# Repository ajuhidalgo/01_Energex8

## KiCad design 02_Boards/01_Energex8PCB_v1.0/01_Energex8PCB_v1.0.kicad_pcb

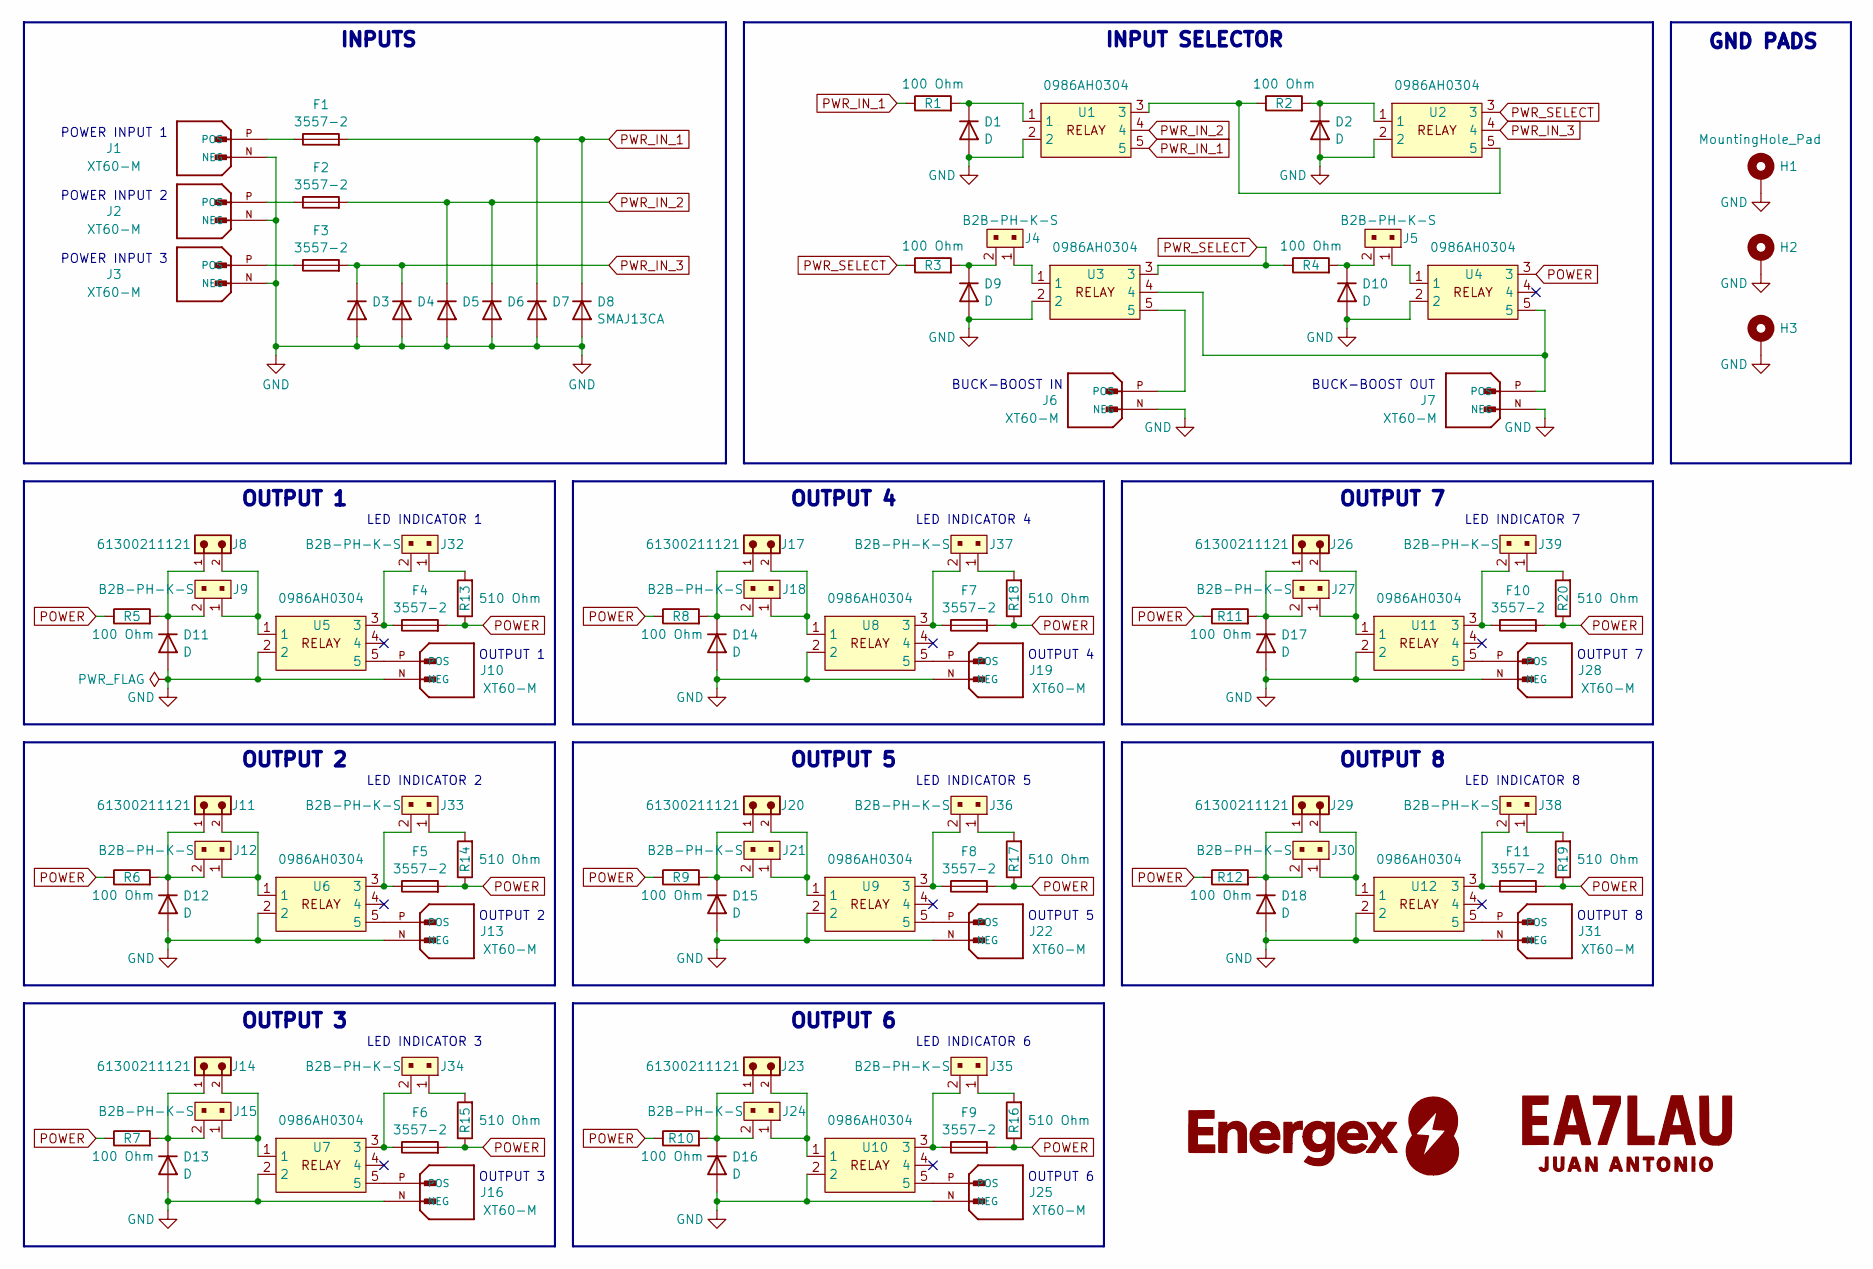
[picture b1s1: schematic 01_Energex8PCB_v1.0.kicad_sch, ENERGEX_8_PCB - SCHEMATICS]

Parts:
D1, D2, D9, D10, D11, D12, D13, D14, D15, D16, D17, D18: D; D_1206_3216Metric
D3, D4, D5, D6, D7, D8: SMAJ13CA; D_SMA
F1, F2, F3, F4, F5, F6, F7, F8, F9, F10, F11: 3557-2; keystone_electronics_3557-2
H1, H2, H3: MountingHole_Pad; MountingHole_3.2mm_M3_Pad_Via
J1, J2, J3, J6, J7, J10, J13, J16, J19, J22, J25, J28, J31: XT60-M; PARTREV V1.2
J4, J5, J9, J12, J15, J18, J21, J24, J27, J30, J32, J33, J34, J35, J36, J37, J38, J39: B2B-PH-K-S; MPN B2B-PH-K-S(LF)(SN); Digi-Key_PN 455-1704-ND
J8, J11, J14, J17, J20, J23, J26, J29: 61300211121; PART-NUMBER 61300211121
R1, R2, R3, R4, R5, R6, R7, R8, R9, R10, R11, R12: 100 Ohm; R_1206_3216Metric
R13, R14, R15, R16, R17, R18, R19, R20: 510 Ohm; R_1206_3216Metric
U1, U2, U3, U4, U5, U6, U7, U8, U9, U10, U11, U12: 0986AH0304

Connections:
GND: D1.2 (A), D2.2 (A), D3.2 (A), D4.2 (A), D5.2 (A), D6.2 (A), D7.2 (A), D8.2 (A), D9.2 (A), D10.2 (A), D11.2 (A), D12.2 (A), D13.2 (A), D14.2 (A), D15.2 (A), D16.2 (A), D17.2 (A), D18.2 (A), H1.1, H2.1, H3.1, J1.N (NEG), J2.N (NEG), J3.N (NEG), J6.N (NEG), J7.N (NEG), J10.N (NEG), J13.N (NEG), J16.N (NEG), J19.N (NEG), J22.N (NEG), J25.N (NEG), J28.N (NEG), J31.N (NEG), U1.2, U2.2, U3.2, U4.2, U5.2, U6.2, U7.2, U8.2, U9.2, U10.2, U11.2, U12.2
unnamed: D1.1 (K), R1.2, U1.1
unnamed: D2.1 (K), R2.2, U2.1
unnamed: D9.1 (K), J4.2, R3.2
unnamed: D10.1 (K), J5.2, R4.2
unnamed: D11.1 (K), J8.1, J9.2, R5.2
unnamed: D12.1 (K), J11.1, J12.2, R6.2
unnamed: D13.1 (K), J14.1, J15.2, R7.2
unnamed: D14.1 (K), J17.1, J18.2, R8.2
unnamed: D15.1 (K), J20.1, J21.2, R9.2
unnamed: D16.1 (K), J23.1, J24.2, R10.2
unnamed: D17.1 (K), J26.1, J27.2, R11.2
unnamed: D18.1 (K), J29.1, J30.2, R12.2
unnamed: F4.1, J32.2, U5.3
unnamed: F5.1, J33.2, U6.3
unnamed: F6.1, J34.2, U7.3
unnamed: F7.1, J37.2, U8.3
unnamed: F8.1, J36.2, U9.3
unnamed: F9.1, J35.2, U10.3
unnamed: F10.1, J39.2, U11.3
unnamed: F11.1, J38.2, U12.3
unnamed: F1.1, J1.P (POS)
unnamed: F2.1, J2.P (POS)
unnamed: F3.1, J3.P (POS)
unnamed: J4.1, U3.1
unnamed: J5.1, U4.1
unnamed: J6.P (POS), U3.5
unnamed: J7.P (POS), U3.4, U4.5
unnamed: J8.2, J9.1, U5.1
unnamed: J10.P (POS), U5.5
unnamed: J11.2, J12.1, U6.1
unnamed: J13.P (POS), U6.5
unnamed: J14.2, J15.1, U7.1
unnamed: J16.P (POS), U7.5
unnamed: J17.2, J18.1, U8.1
unnamed: J19.P (POS), U8.5
unnamed: J20.2, J21.1, U9.1
unnamed: J22.P (POS), U9.5
unnamed: J23.2, J24.1, U10.1
unnamed: J25.P (POS), U10.5
unnamed: J26.2, J27.1, U11.1
unnamed: J28.P (POS), U11.5
unnamed: J29.2, J30.1, U12.1
unnamed: J31.P (POS), U12.5
unnamed: J32.1, R13.2
unnamed: J33.1, R14.2
unnamed: J34.1, R15.2
unnamed: J35.1, R16.2
unnamed: J36.1, R17.2
unnamed: J37.1, R18.2
unnamed: J38.1, R19.2
unnamed: J39.1, R20.2
unnamed: R2.1, U1.3, U2.5
POWER: F4.2, F5.2, F6.2, F7.2, F8.2, F9.2, F10.2, F11.2, R5.1, R6.1, R7.1, R8.1, R9.1, R10.1, R11.1, R12.1, R13.1, R14.1, R15.1, R16.1, R17.1, R18.1, R19.1, R20.1, U4.3
PWR_IN_1: D7.1 (K), D8.1 (K), F1.2, R1.1, U1.5
PWR_IN_2: D5.1 (K), D6.1 (K), F2.2, U1.4
PWR_IN_3: D3.1 (K), D4.1 (K), F3.2, U2.4
PWR_SELECT: R3.1, R4.1, U2.3, U3.3

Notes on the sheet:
OUTPUT 6
OUTPUT 3
OUTPUT 8
POWER INPUT 1
OUTPUT 1
LED INDICATOR 6
LED INDICATOR 7
LED INDICATOR 8
OUTPUT 7
LED INDICATOR 4
OUTPUT 4
GND PADS
OUTPUT 5
BUCK-BOOST OUT
LED INDICATOR 1
INPUT SELECTOR
INPUTS
POWER INPUT 3
LED INDICATOR 2
LED INDICATOR 3
LED INDICATOR 5
BUCK-BOOST IN
OUTPUT 2
POWER INPUT 2

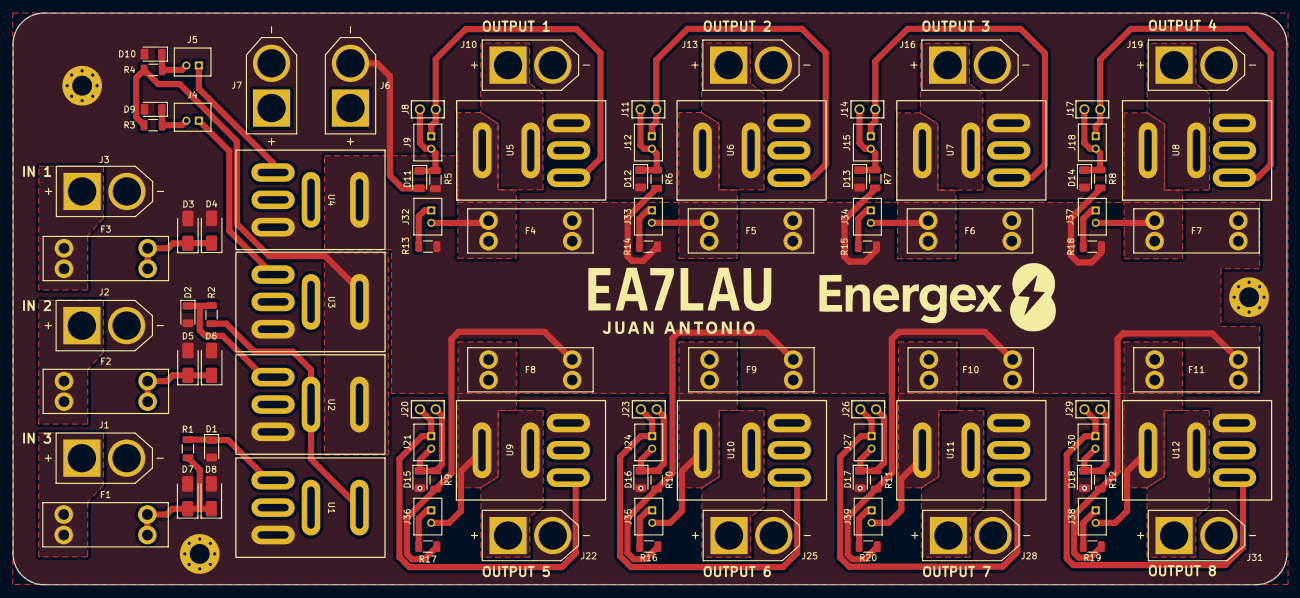
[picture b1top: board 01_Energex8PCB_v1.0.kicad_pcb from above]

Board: 4 copper layers, 205.0 x 92.0 mm, 103 parts (0 on the bottom side), 58 nets.

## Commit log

2025-06-06 Create repository
2025-06-06 Images
2025-06-06 PCB Documentation
2025-06-06 Relative routes
2025-06-14 New BoM
